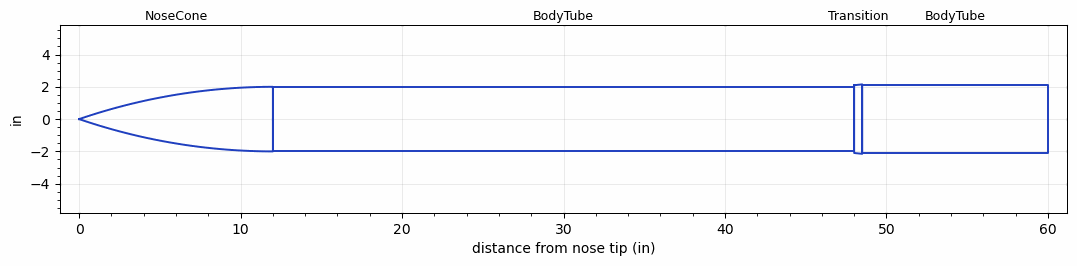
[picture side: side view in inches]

<RASAeroDocument>
 <FileVersion>2</FileVersion>
 <RocketDesign>
  <NoseCone>
   <Length>12</Length>
   <Diameter>4</Diameter>
   <Shape>Tangent Ogive</Shape>
   <Location>0</Location>
  </NoseCone>
  <BodyTube>
   <Length>36.0</Length>
   <Diameter>4</Diameter>
   <Location>12</Location>
  </BodyTube>
  <Transition>
   <Length>0.5</Length>
   <Diameter>4.2</Diameter>
   <Location>48.0</Location>
   <RearDiameter>4.3</RearDiameter>
  </Transition>
  <BodyTube>
   <Length>11.5</Length>
   <Diameter>4.2</Diameter>
   <Location>48.5</Location>
  </BodyTube>
  <Surface>Smooth (Zero Roughness)</Surface>
  <ModifiedBarrowman>False</ModifiedBarrowman>
  <Turbulence>True</Turbulence>
  <UseBooster1>False</UseBooster1>
  <UseBooster2>False</UseBooster2>
  <Comments>Afterbody component study A-step</Comments>
 </RocketDesign>
 <LaunchSite>
  <Altitude>0</Altitude>
  <Pressure>29.9214</Pressure>
  <RodAngle>0</RodAngle>
  <RodLength>6.5617</RodLength>
  <Temperature>59</Temperature>
  <WindSpeed>0</WindSpeed>
 </LaunchSite>
 <Recovery>
  <Altitude1>656.168</Altitude1>
  <Altitude2>0</Altitude2>
  <DeviceType1>Parachute</DeviceType1>
  <DeviceType2>None</DeviceType2>
  <Event1>True</Event1>
  <Event2>False</Event2>
  <Size1>24</Size1>
  <Size2>0</Size2>
  <EventType1>Apogee</EventType1>
  <EventType2>None</EventType2>
  <CD1>0.8</CD1>
  <CD2>0</CD2>
 </Recovery>
</RASAeroDocument>
